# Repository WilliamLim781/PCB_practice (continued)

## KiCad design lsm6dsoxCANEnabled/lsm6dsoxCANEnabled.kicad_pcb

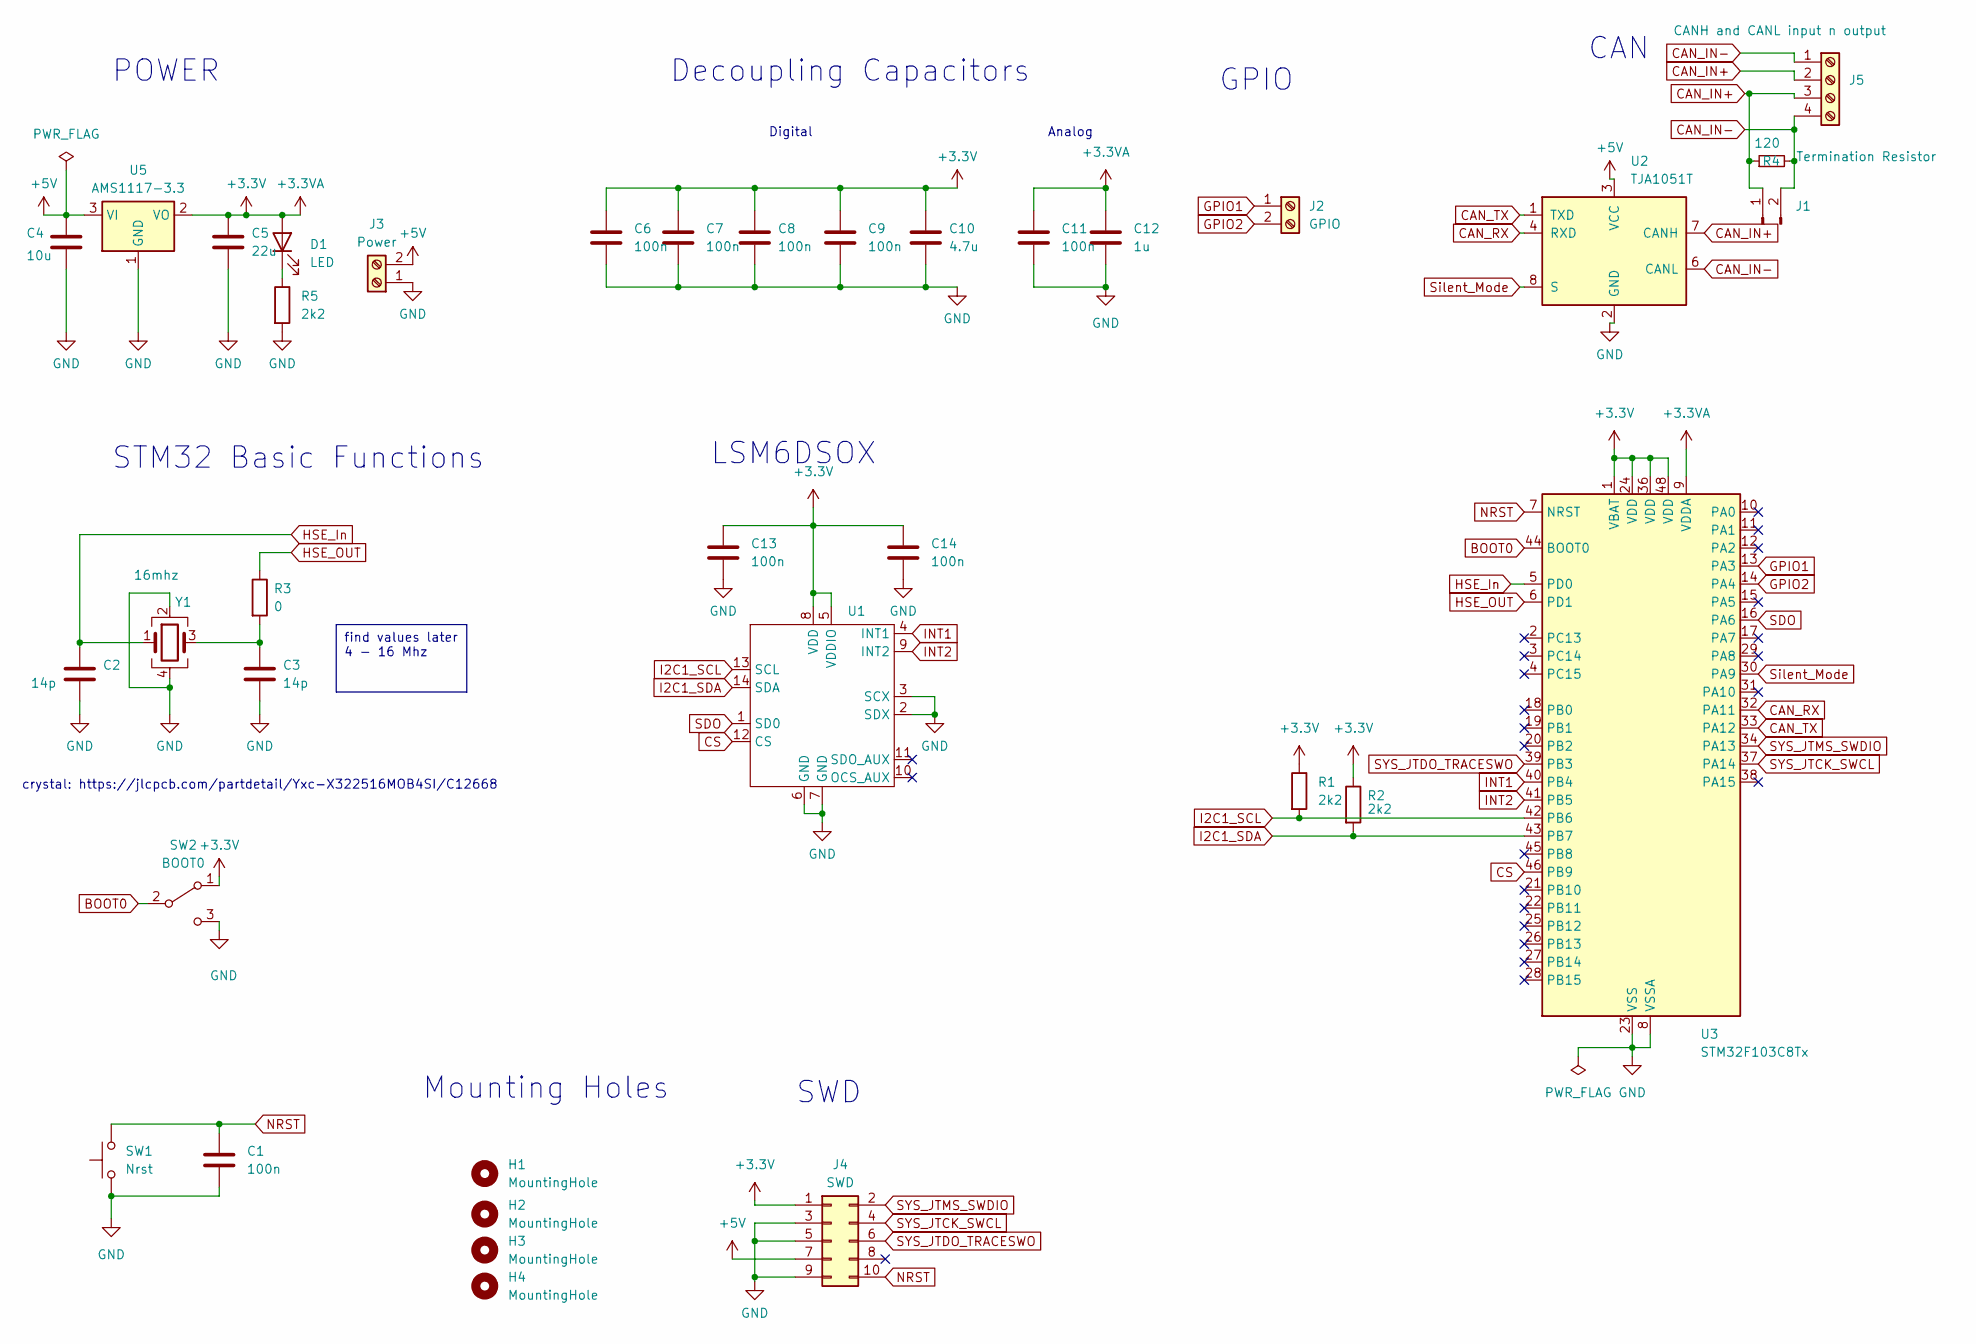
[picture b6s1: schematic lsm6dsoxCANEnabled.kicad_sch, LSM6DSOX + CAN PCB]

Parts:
C1, C6, C7, C8, C9, C11, C13, C14: 100n; C_0603_1608Metric_Pad1.08x0.95mm_HandSolder
C2, C3: 14p; C_0603_1608Metric_Pad1.08x0.95mm_HandSolder
C4: 10u; C_0603_1608Metric_Pad1.08x0.95mm_HandSolder
C5: 22u; C_0805_2012Metric_Pad1.18x1.45mm_HandSolder
C10: 4.7u; C_0603_1608Metric_Pad1.08x0.95mm_HandSolder
C12: 1u; C_0603_1608Metric_Pad1.08x0.95mm_HandSolder
D1: LED; LED_0603_1608Metric_Pad1.05x0.95mm_HandSolder
H1, H2, H3, H4: MountingHole; MountingHole_4mm_Pad_Via
J1: Termination Resistor; PinHeader_1x02_P2.54mm_Vertical
J2: GPIO; TerminalBlock_Phoenix_MKDS-1,5-2_1x02_P5.00mm_Horizontal
J3: Power; TerminalBlock_Phoenix_MKDS-1,5-2_1x02_P5.00mm_Horizontal
J4: SWD; PinHeader_2x05_P2.54mm_Vertical
J5: CANH and CANL input n output; TerminalBlock_Phoenix_MKDS-1,5-4_1x04_P5.00mm_Horizontal
R1, R2, R5: 2k2; R_0603_1608Metric_Pad0.98x0.95mm_HandSolder
R3: 0; R_0603_1608Metric_Pad0.98x0.95mm_HandSolder
R4: 120; R_0603_1608Metric_Pad0.98x0.95mm_HandSolder
SW1: Nrst; SW_SPST_PTS645
SW2: BOOT0; SW_SPDT_CK-JS102011SAQN
U1: LGA-14_3x2.5mm_P0.5mm_LayoutBorder3x4y
U2: TJA1051T; SOIC-8_3.9x4.9mm_P1.27mm
U3: STM32F103C8Tx; LQFP-48_7x7mm_P0.5mm
U5: AMS1117-3.3; SOT-223-3_TabPin2
Y1: 16mhz; Crystal_SMD_3225-4Pin_3.2x2.5mm_HandSoldering

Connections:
+3.3V: C5.1, C6.1, C7.1, C8.1, C9.1, C10.1, C11.1, C12.1, C13.1, C14.1, D1.2 (A), J4.1, R1.1, R2.1, SW2.1 (A), U1.5 (VDDIO), U1.8 (VDD), U3.1 (VBAT), U3.9 (VDDA), U3.24 (VDD), U3.36 (VDD), U3.48 (VDD), U5.2 (VO)
+5V: C4.1, J3.2, J4.7, U2.3 (VCC), U5.3 (VI)
BOOT0: SW2.2 (B), U3.44 (BOOT0)
CAN_IN+: J1.1, J5.2, J5.3, R4.1, U2.7 (CANH)
CAN_IN-: J1.2, J5.1, J5.4, R4.2, U2.6 (CANL)
CAN_RX: U2.4 (RXD), U3.32 (PA11)
CAN_TX: U2.1 (TXD), U3.33 (PA12)
CS: U1.12 (CS), U3.46 (PB9)
GND: C1.2, C2.2, C3.2, C4.2, C5.2, C6.2, C7.2, C8.2, C9.2, C10.2, C11.2, C12.2, C13.2, C14.2, J3.1, J4.3, J4.5, J4.9, R5.2, SW1.1, SW2.3 (C), U1.2 (SDX), U1.3 (SCX), U1.6 (GND), U1.7 (GND), U2.2 (GND), U3.8 (VSSA), U3.23 (VSS), U3.35 (VSS), U3.47 (VSS), U5.1 (GND), Y1.2, Y1.4
GPIO1: J2.1, U3.13 (PA3)
GPIO2: J2.2, U3.14 (PA4)
HSE_In: C2.1, U3.5 (PD0), Y1.1
HSE_OUT: R3.1, U3.6 (PD1)
I2C1_SCL: R1.2, U1.13 (SCL), U3.42 (PB6)
I2C1_SDA: R2.2, U1.14 (SDA), U3.43 (PB7)
INT1: U1.4 (INT1), U3.40 (PB4)
INT2: U1.9 (INT2), U3.41 (PB5)
NRST: C1.1, J4.10, SW1.2, U3.7 (NRST)
unnamed: C3.1, R3.2, Y1.3
unnamed: D1.1 (K), R5.1
SDO: U1.1 (SD0), U3.16 (PA6)
SYS_JTCK_SWCL: J4.4, U3.37 (PA14)
SYS_JTDO_TRACESWO: J4.6, U3.39 (PB3)
SYS_JTMS_SWDIO: J4.2, U3.34 (PA13)
Silent_Mode: U2.8 (S), U3.30 (PA9)

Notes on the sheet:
find values later 4 - 16 Mhz
GPIO
Decoupling Capacitors
crystal: https://jlcpcb.com/partdetail/Yxc-X322516MOB4SI/C12668
SWD
Analog
LSM6DSOX
Mounting Holes
Digital
POWER
STM32 Basic Functions
CAN

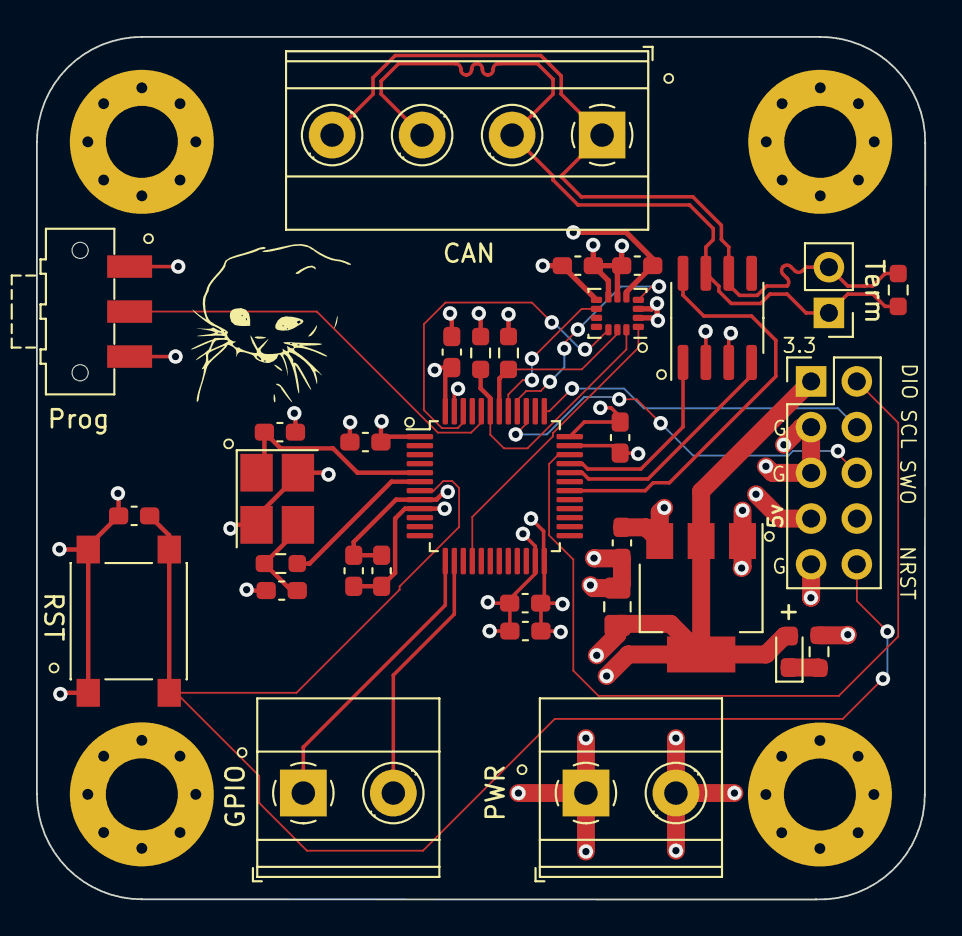
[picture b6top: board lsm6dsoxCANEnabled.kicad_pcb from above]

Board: 4 copper layers, 49.4 x 47.9 mm, 36 parts (0 on the bottom side), 25 nets.

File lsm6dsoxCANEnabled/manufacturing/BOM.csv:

Comment,Designator,FootPrint,JLCPCB PART#
100n,"C1, C6,C7,C8,C9, C11, C13, C14",Capacitor_SMD:C_0603_1608Metric_Pad1.08x0.95mm_HandSolder,C14663
14p,"C2, C3",Capacitor_SMD:C_0603_1608Metric_Pad1.08x0.95mm_HandSolder,C126546
10u,C4,Capacitor_SMD:C_0603_1608Metric_Pad1.08x0.95mm_HandSolder,C386081
22u,C5,Capacitor_SMD:C_0805_2012Metric_Pad1.18x1.45mm_HandSolder,C318688
4.7u,C10,Capacitor_SMD:C_0603_1608Metric_Pad1.08x0.95mm_HandSolder,C711094
1u,C12,Capacitor_SMD:C_0603_1608Metric_Pad1.08x0.95mm_HandSolder,C106858
LED,D1,LED_SMD:LED_0603_1608Metric_Pad1.05x0.95mm_HandSolder,C2290
MountingHole,H1-H4,MountingHole:MountingHole_4mm_Pad_Via,
Termination Resistor ,J1,Connector_PinHeader_2.54mm:PinHeader_1x02_P2.54mm_Vertical,
GPIO,J2,"TerminalBlock_Phoenix:TerminalBlock_Phoenix_MKDS-1,5-2_1x02_P5.00mm_Horizontal",
Power,J3,"TerminalBlock_Phoenix:TerminalBlock_Phoenix_MKDS-1,5-2_1x02_P5.00mm_Horizontal",
SWD,J4,Connector_PinHeader_2.54mm:PinHeader_2x05_P2.54mm_Vertical,
CANH and CANL input n output,J5,"TerminalBlock_Phoenix:TerminalBlock_Phoenix_MKDS-1,5-4_1x04_P5.00mm_Horizontal",
2k2,"R1, R2, R5",Resistor_SMD:R_0603_1608Metric_Pad0.98x0.95mm_HandSolder,C4190
0,R3,Resistor_SMD:R_0603_1608Metric_Pad0.98x0.95mm_HandSolder,C21189
120,R4,Resistor_SMD:R_0603_1608Metric_Pad0.98x0.95mm_HandSolder,C22787
Nrst,SW1,Button_Switch_SMD:SW_SPST_PTS645,C2801823
BOOT0 ,SW2,Button_Switch_SMD:SW_SPDT_CK-JS102011SAQN,C221660
LSM6DSOX,U1,Package_LGA:LGA-14_3x2.5mm_P0.5mm_LayoutBorder3x4y,C481766
TJA1051T,U2,Package_SO:SOIC-8_3.9x4.9mm_P1.27mm,"
C7432801"
STM32F103C8Tx,U3,Package_QFP:LQFP-48_7x7mm_P0.5mm,C8734
AMS1117CD-3.3,    U5,Package_TO_SOT_SMD:SOT-223-3_TabPin2,C6186
16mhz,Y1,Crystal:Crystal_SMD_3225-4Pin_3.2x2.5mm_HandSoldering,C12668

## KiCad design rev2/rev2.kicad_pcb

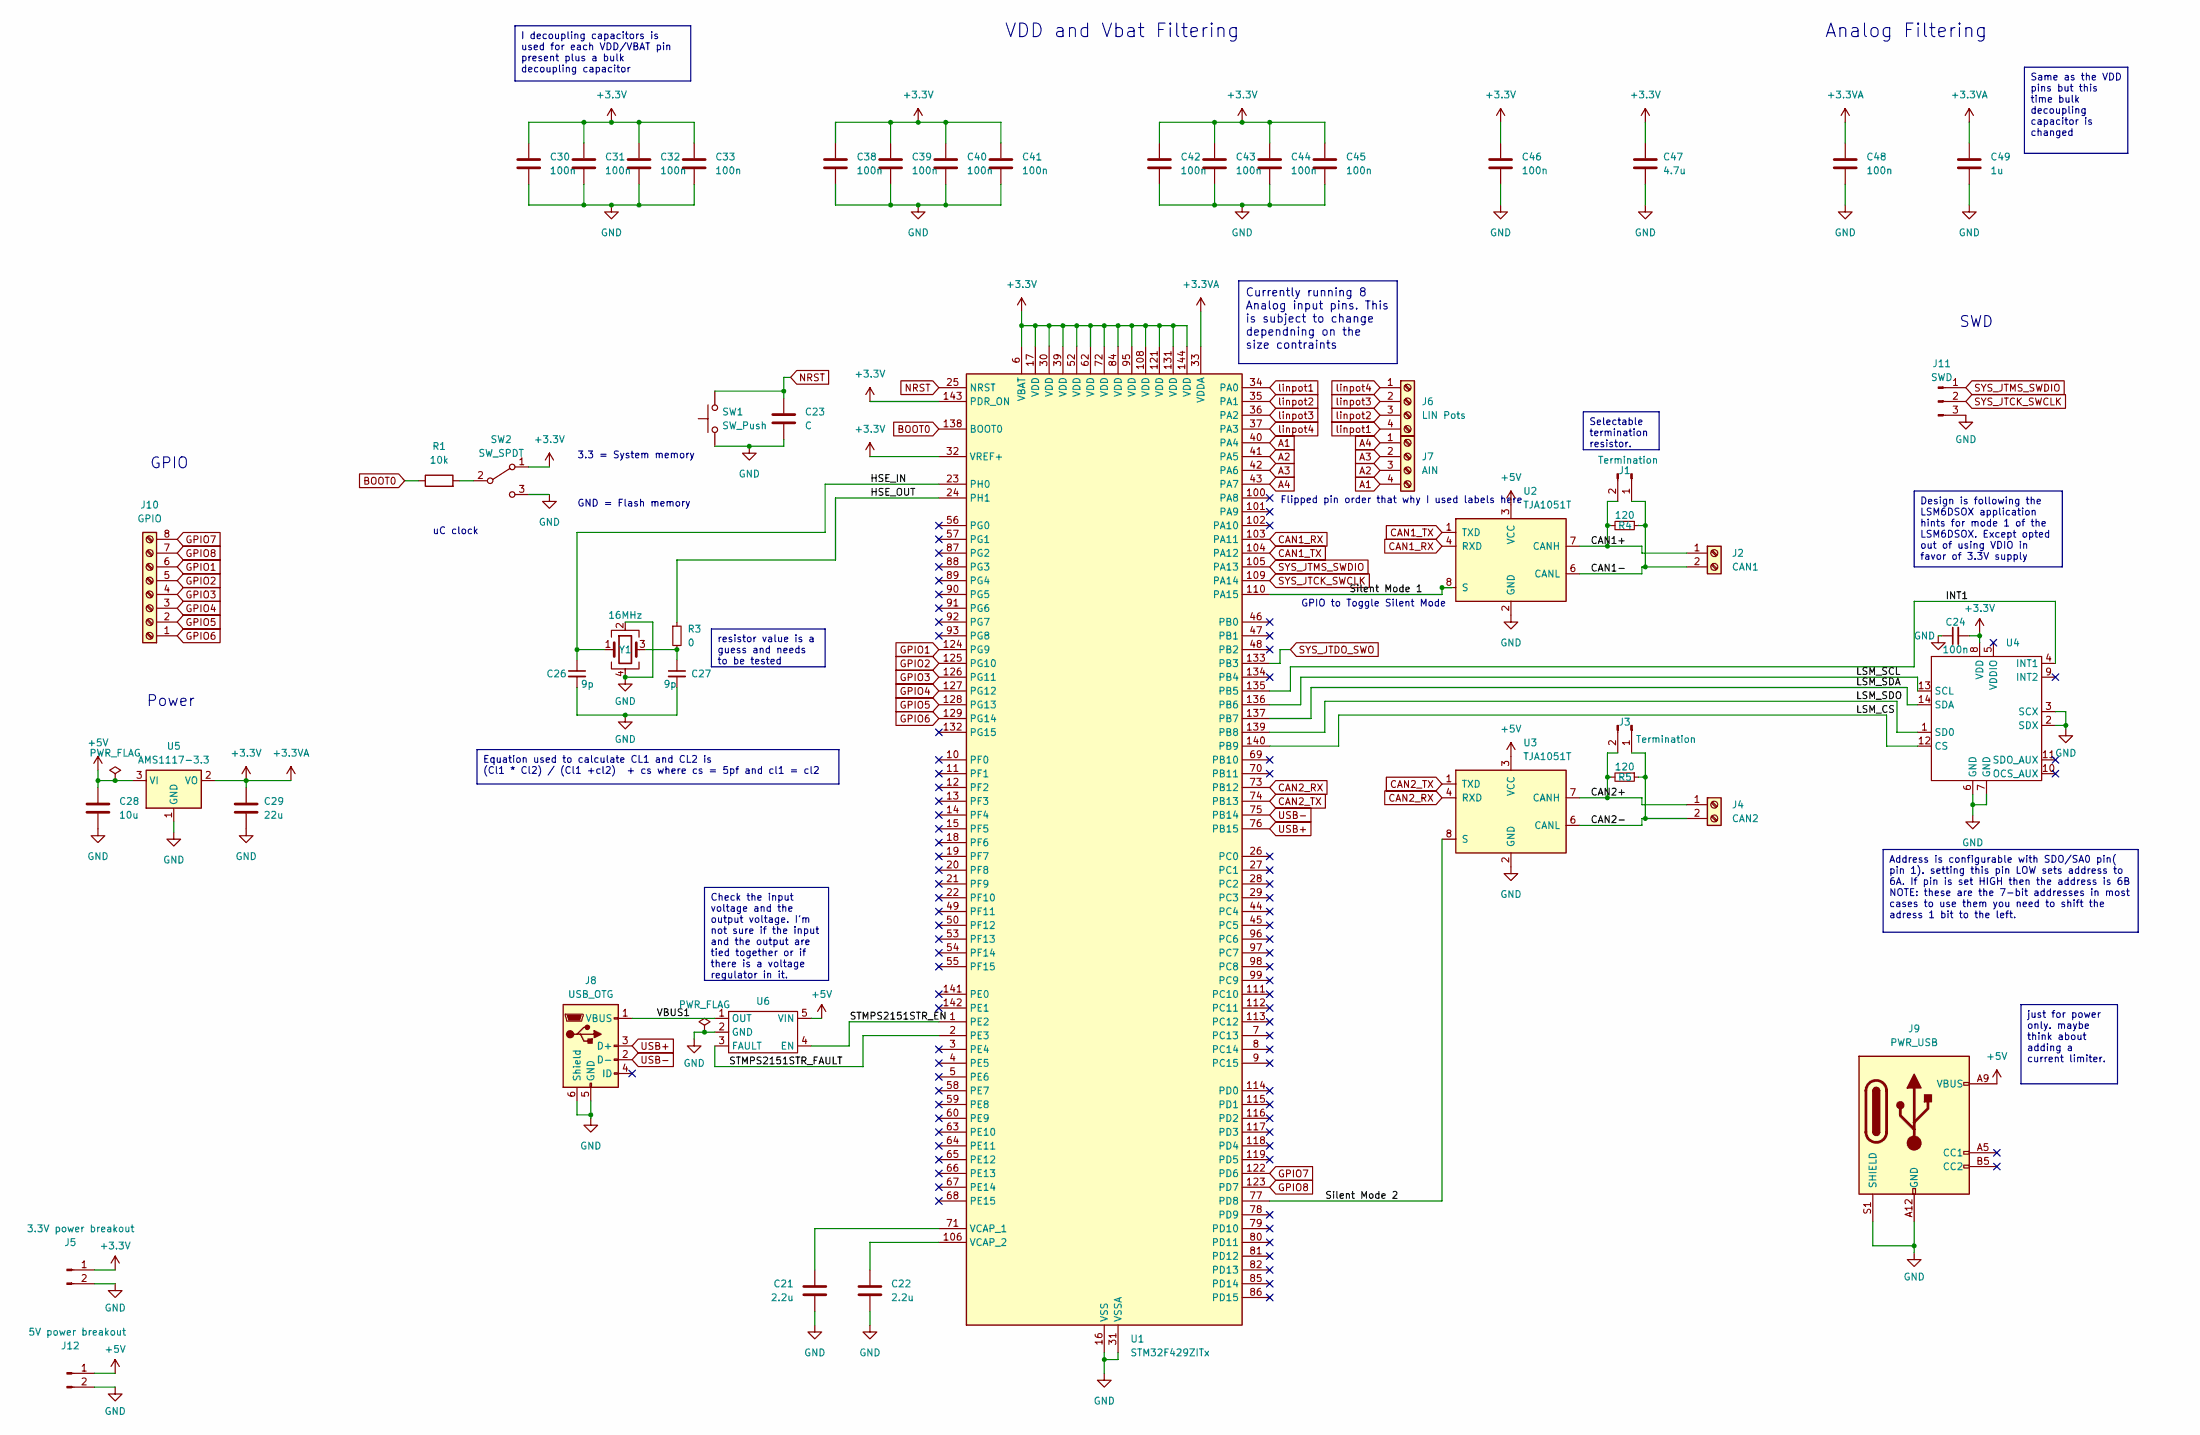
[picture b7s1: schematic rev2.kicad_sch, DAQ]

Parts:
C21, C22: 2.2u; C_0603_1608Metric_Pad1.08x0.95mm_HandSolder
C23: C; C_0603_1608Metric_Pad1.08x0.95mm_HandSolder
C24, C30, C31, C32, C33, C38, C39, C40, C41, C42, C43, C44, C45, C46, C48: 100n; C_0603_1608Metric_Pad1.08x0.95mm_HandSolder
C26, C27: 9p; C_0603_1608Metric_Pad1.08x0.95mm_HandSolder
C28: 10u; C_0603_1608Metric_Pad1.08x0.95mm_HandSolder
C29: 22u; C_0603_1608Metric_Pad1.08x0.95mm_HandSolder
C47: 4.7u; C_0603_1608Metric_Pad1.08x0.95mm_HandSolder
C49: 1u; C_0603_1608Metric_Pad1.08x0.95mm_HandSolder
J1, J3: Termination; PinHeader_1x02_P2.54mm_Vertical
J2: CAN1; TerminalBlock_Phoenix_MPT-0,5-2-2.54_1x02_P2.54mm_Horizontal
J4: CAN2; TerminalBlock_Phoenix_MPT-0,5-2-2.54_1x02_P2.54mm_Horizontal
J5: 3.3V power breakout; PinHeader_1x02_P2.54mm_Vertical
J6: LIN Pots; TerminalBlock_Phoenix_MPT-0,5-4-2.54_1x04_P2.54mm_Horizontal
J7: AIN; TerminalBlock_Phoenix_MPT-0,5-4-2.54_1x04_P2.54mm_Horizontal
J8: USB_OTG; USB_Mini-B_Wuerth_65100516121_Horizontal
J9: PWR_USB; USB_C_Receptacle_GCT_USB4105-xx-A_16P_TopMnt_Horizontal
J10: GPIO; TerminalBlock_Phoenix_MPT-0,5-8-2.54_1x08_P2.54mm_Horizontal
J11: SWD; PinHeader_1x03_P2.54mm_Vertical
J12: 5V power breakout; PinHeader_1x02_P2.54mm_Vertical
R1: 10k; R_0603_1608Metric_Pad0.98x0.95mm_HandSolder
R3: 0; R_0603_1608Metric_Pad0.98x0.95mm_HandSolder
R4, R5: 120; R_0603_1608Metric_Pad0.98x0.95mm_HandSolder
SW1: SW_Push; SW_SPST_PTS645
SW2: SW_SPDT; SW_SPDT_PCM12
U1: STM32F429ZITx; LQFP-144_20x20mm_P0.5mm
U2, U3: TJA1051T; SOIC-8_3.9x4.9mm_P1.27mm
U4: Bosch_LGA-14_3x2.5mm_P0.5mm
U5: AMS1117-3.3; SOT-223-3_TabPin2
U6: SOT-23-5_HandSoldering
Y1: 16MHz; Crystal_SMD_3225-4Pin_3.2x2.5mm

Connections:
+3.3V: C24.2, C29.1, C30.1, C31.1, C32.1, C33.1, C38.1, C39.1, C40.1, C41.1, C42.1, C43.1, C44.1, C45.1, C46.1, C47.1, C48.1, C49.1, J5.1, SW2.1 (A), U1.6 (VBAT), U1.17 (VDD), U1.30 (VDD), U1.32 (VREF+), U1.33 (VDDA), U1.39 (VDD), U1.52 (VDD), U1.62 (VDD), U1.72 (VDD), U1.84 (VDD), U1.95 (VDD), U1.108 (VDD), U1.121 (VDD), U1.131 (VDD), U1.143 (PDR_ON), U1.144 (VDD), U4.8 (VDD), U5.2 (VO)
+5V: C28.1, J9.A9 (VBUS), J9.B9 (VBUS), J12.1, U2.3 (VCC), U3.3 (VCC), U5.3 (VI), U6.5 (VIN)
/CAN1+: J1.2, J2.1, R4.2, U2.7 (CANH)
/CAN1-: J1.1, J2.2, R4.1, U2.6 (CANL)
/CAN2+: J3.2, J4.1, R5.2, U3.7 (CANH)
/CAN2-: J3.1, J4.2, R5.1, U3.6 (CANL)
/HSE_IN: C26.1, U1.23 (PH0), Y1.1
/HSE_OUT: R3.1, U1.24 (PH1)
/INT1: U1.135 (PB5), U4.4 (INT1)
/LSM_CS: U1.140 (PB9), U4.12 (CS)
/LSM_SCL: U1.136 (PB6), U4.13 (SCL)
/LSM_SDA: U1.137 (PB7), U4.14 (SDA)
/LSM_SDO: U1.139 (PB8), U4.1 (SD0)
/STMPS2151STR_EN: U1.1 (PE2), U6.4 (EN)
/STMPS2151STR_FAULT: U1.2 (PE3), U6.3 (FAULT)
/Silent Mode 1: U1.110 (PA15), U2.8 (S)
/Silent Mode 2: U1.77 (PD8), U3.8 (S)
/VBUS1: J8.1 (VBUS), U6.1 (OUT)
A1: J7.4, U1.40 (PA4)
A2: J7.3, U1.41 (PA5)
A3: J7.2, U1.42 (PA6)
A4: J7.1, U1.43 (PA7)
BOOT0: R1.1, U1.138 (BOOT0)
CAN1_RX: U1.103 (PA11), U2.4 (RXD)
CAN1_TX: U1.104 (PA12), U2.1 (TXD)
CAN2_RX: U1.73 (PB12), U3.4 (RXD)
CAN2_TX: U1.74 (PB13), U3.1 (TXD)
GND: C21.2, C22.2, C23.2, C24.1, C26.2, C27.2, C28.2, C29.2, C30.2, C31.2, C32.2, C33.2, C38.2, C39.2, C40.2, C41.2, C42.2, C43.2, C44.2, C45.2, C46.2, C47.2, C48.2, C49.2, J5.2, J8.5 (GND), J8.6 (Shield), J9.A12 (GND), J9.B12 (GND), J9.S1 (SHIELD), J11.3, J12.2, SW1.1, SW2.3 (C), U1.16 (VSS), U1.31 (VSSA), U1.38 (VSS), U1.51 (VSS), U1.61 (VSS), U1.83 (VSS), U1.94 (VSS), U1.107 (VSS), U1.120 (VSS), U1.130 (VSS), U2.2 (GND), U3.2 (GND), U4.2 (SDX), U4.3 (SCX), U4.6 (GND), U4.7 (GND), U5.1 (GND), U6.2 (GND), Y1.2, Y1.4
GPIO1: J10.6, U1.124 (PG9)
GPIO2: J10.5, U1.125 (PG10)
GPIO3: J10.4, U1.126 (PG11)
GPIO4: J10.3, U1.127 (PG12)
GPIO5: J10.2, U1.128 (PG13)
GPIO6: J10.1, U1.129 (PG14)
GPIO7: J10.8, U1.122 (PD6)
GPIO8: J10.7, U1.123 (PD7)
NRST: C23.1, SW1.2, U1.25 (NRST)
unnamed: C27.1, R3.2, Y1.3
unnamed: R1.2, SW2.2 (B)
unnamed: C21.1, U1.71 (VCAP_1)
unnamed: C22.1, U1.106 (VCAP_2)
SYS_JTCK_SWCLK: J11.2, U1.109 (PA14)
SYS_JTDO_SWO: U1.133 (PB3)
SYS_JTMS_SWDIO: J11.1, U1.105 (PA13)
USB+: J8.3 (D+), U1.76 (PB15)
USB-: J8.2 (D-), U1.75 (PB14)
linpot1: J6.4, U1.34 (PA0)
linpot2: J6.3, U1.35 (PA1)
linpot3: J6.2, U1.36 (PA2)
linpot4: J6.1, U1.37 (PA3)

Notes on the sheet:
Design is following the LSM6DSOX application hints for mode 1 of the LSM6DSOX. Except opted out of using VDIO in favor of 3.3V supply
resistor value is a guess and needs to be tested
just for power only. maybe think about adding a current limiter.
Check the input voltage and the output voltage. I'm not sure if the input and the output are tied together or if there is a voltage regulator in it.
Equation used to calculate CL1 and CL2 is (Cl1 * Cl2) / (Cl1 +cl2) + cs where cs = 5pf and cl1 = cl2
Currently running 8 Analog input pins. This is subject to change dependning on the size contraints
Selectable termination resistor.
Address is configurable with SDO/SA0 pin( pin 1). setting this pin LOW sets address to 6A. If pin is set HIGH then the address is 6B NOTE: these are the 7-bit addresses in most cases to use them you need to shift the adress 1 bit to the left.
I decoupling capacitors is used for each VDD/VBAT pin present plus a bulk decoupling capacitor
Same as the VDD pins but this time bulk decoupling capacitor is changed
GPIO
3.3 = System memory
Flipped pin order that why I used labels here
SWD
GPIO to Toggle Silent Mode
uC clock
VDD and Vbat Filtering
Analog Filtering
Power
GND = Flash memory

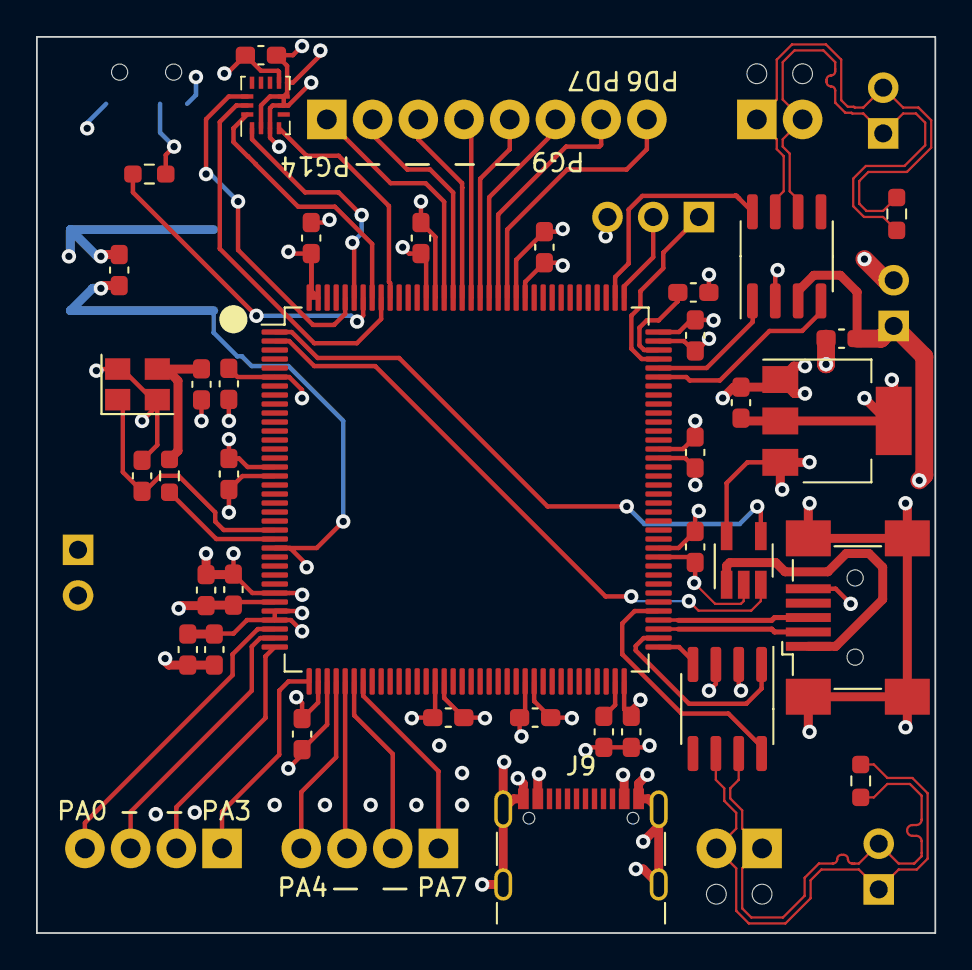
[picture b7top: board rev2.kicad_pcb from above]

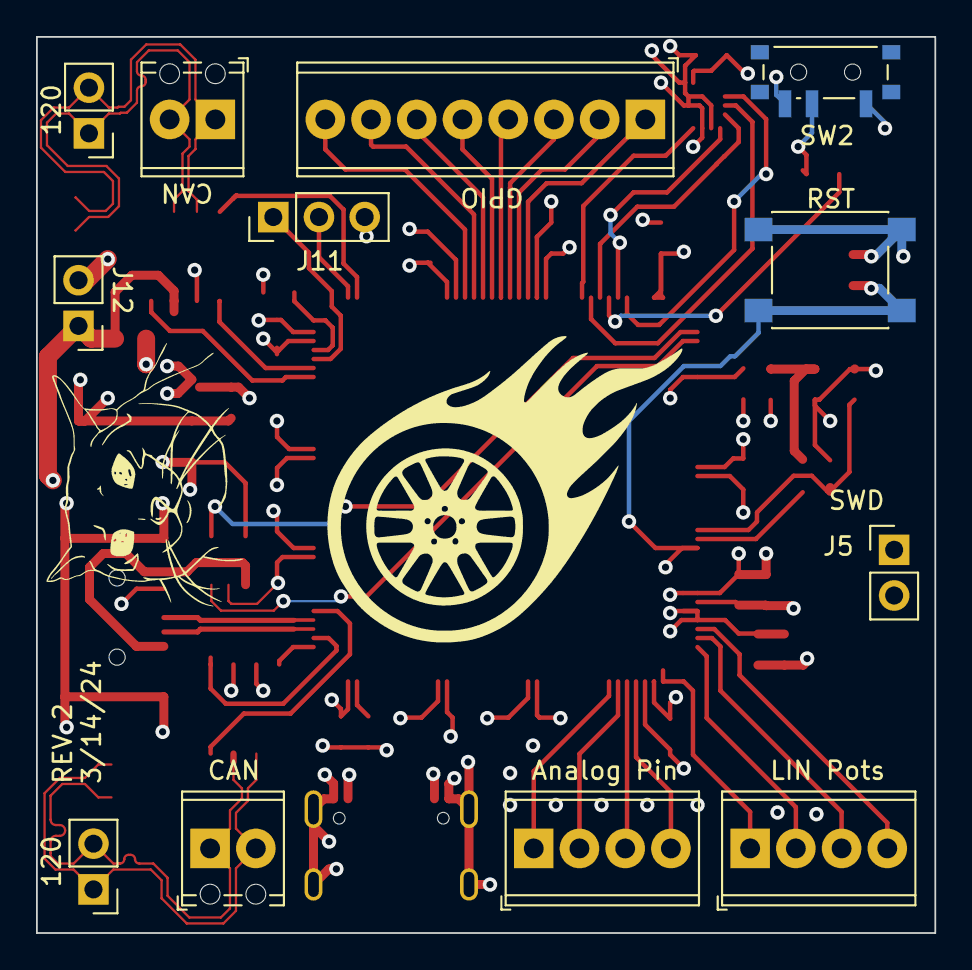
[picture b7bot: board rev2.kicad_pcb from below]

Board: 4 copper layers, 49.9 x 49.8 mm, 49 parts (12 on the bottom side), 49 nets.

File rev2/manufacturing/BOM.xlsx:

Comment | Designator | FootPrint | JLCPCB PART#
2.2u | C21,C22,C23 | 603 | C76612
100n | C24, C30-33, C38-46, C48 | 603 | C88219
9p | C26,C27 | 603 | C282512
10u | C28 | 603 | C91150
22u | C29 | 603 | C84419
4.7u | C47 | 603 | C86016
1u | C49 | 603 | C76617
STM32F429ZITx | U1 | LQFP144 | C84808
USB_OTG | J8
PWR_USB | J9
10k | R1 | 603 | C191124
120 | R4, R5 | 603 | C177673
0 | R3 | 603
SW_Push | SW1 | SPST_PTS645
SW2 | SW_SPDT | PCM12
TJA1051T | U2, U3 | SOIC-8 | C5342108
LSM6DSOX | U4 | LGA-14 | C481766
AMS1117-3.3 | U5 | SOT-223-3 | C6186
 | U6 | SOT-23 | C135998
16MHz | Y1 | SMD_3225

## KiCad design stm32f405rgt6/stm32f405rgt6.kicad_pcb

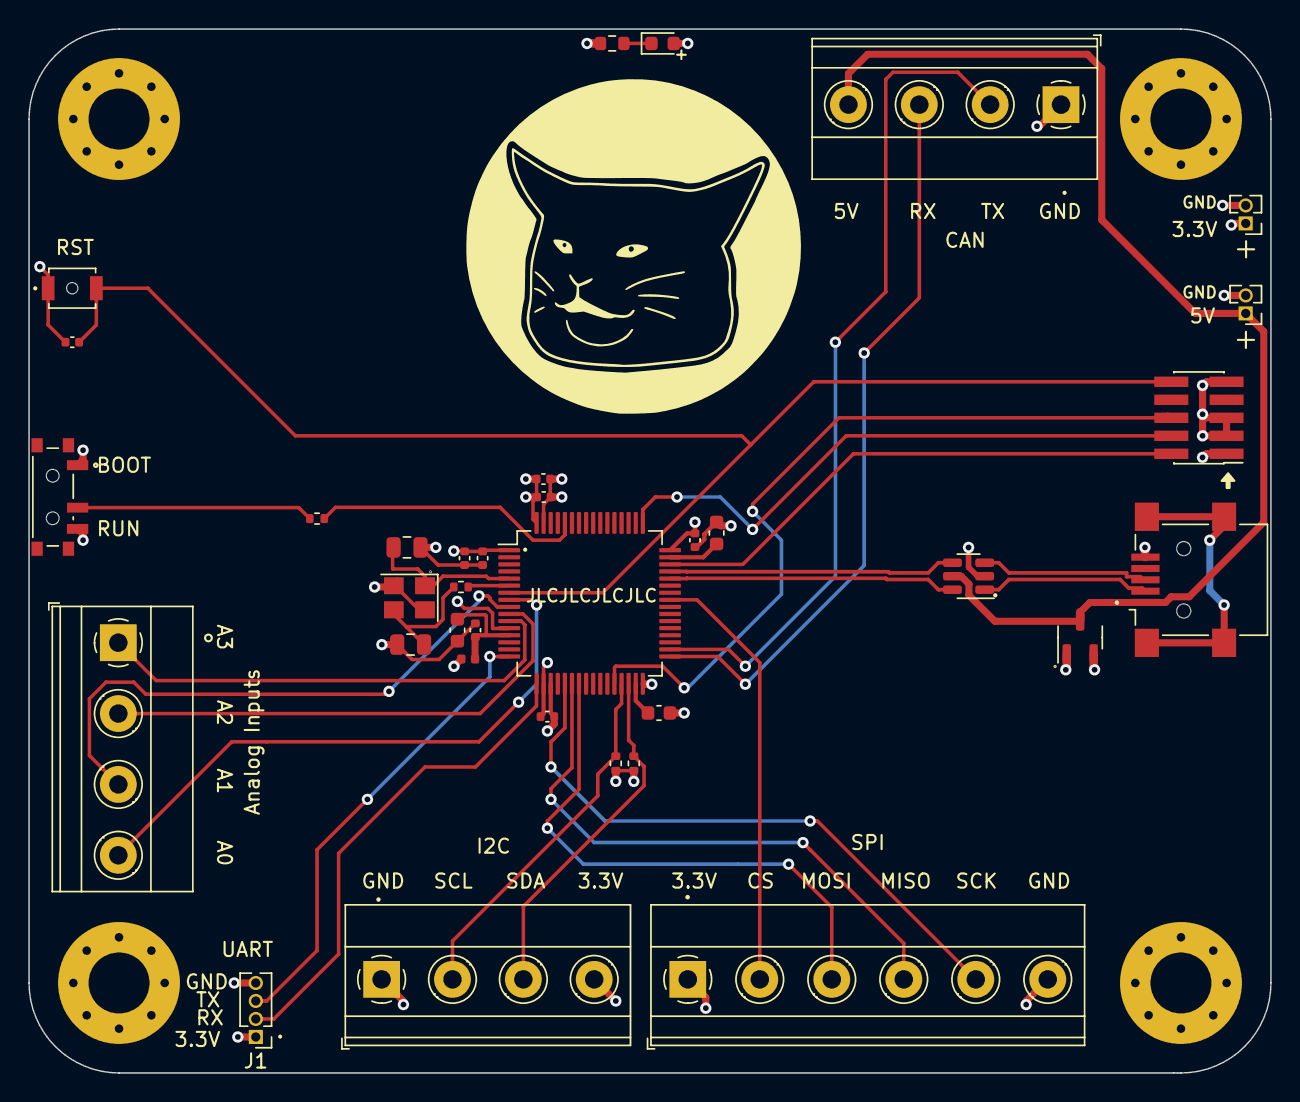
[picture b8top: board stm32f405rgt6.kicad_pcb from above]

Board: 4 copper layers, 87.6 x 73.7 mm, 39 parts (0 on the bottom side), 34 nets.

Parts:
Analog Inputs: AnalogInptus; TerminalBlock_Phoenix_MKDS-1,5-4_1x04_P5.00mm_Horizontal
C1: 1u; C_0402_1005Metric
C2, C3, C4, C5, C6: 100n; C_0402_1005Metric
C7: 4u7; C_0603_1608Metric
C8: 10n; C_0402_1005Metric
C9: .1u; C_0402_1005Metric
C10, C11: 14pf; C_0805_2012Metric
C12, C13: 2u2; C_0603_1608Metric
D1: LED; LED_0603_1608Metric
H1, H2, H3, H4: MountingHole_Pad; MountingHole_4.3mm_M4_Pad_Via
I2C: I2C; TerminalBlock_Phoenix_MKDS-1,5-4_1x04_P5.00mm_Horizontal
J1: USART; PinHeader_1x04_P1.27mm_Vertical
J2: SWD; PinHeader_2x05_P1.27mm_Vertical_SMD
J4: USB_OTG; USB_Mini-B_Lumberg_2486_01_Horizontal
J7: 5V; PinHeader_1x02_P1.27mm_Vertical
J8: CAN; TerminalBlock_Phoenix_MKDS-1,5-4_1x04_P5.00mm_Horizontal
J9: 3.3V; PinHeader_1x02_P1.27mm_Vertical
L1: 39n; L_0402_1005Metric
R1, R2: 2k2; R_0402_1005Metric
R3: 10k; R_0402_1005Metric
R4: 47; R_0402_1005Metric
R5: 1k5; R_0603_1608Metric
SPI: SPI; TerminalBlock_Phoenix_MKDS-1,5-6-5.08_1x06_P5.08mm_Horizont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
SW1: SW_Push; SW_SPST_B3U-1000P-B
SW2: Boot0 selector; SW_SPDT_PCM12
U1: USBLC6-2SC6; SOT-23-6
U2: STM32F405RGT6; LQFP-64_10x10mm_P0.5mm
XC6206P332MR1: SOT-23-3
Y1: 25Mhz; Crystal_SMD_3225-4Pin_3.2x2.5mm

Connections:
+3.3V: C1.1, C2.1, C3.1, C4.1, C5.1, C6.1, D1.2 (A), I2C.4, J1.1, J2.1, J9.1, L1.1, R1.2, R2.1, SPI.1, SW2.1 (A), U2.1 (VBAT), U2.19 (VDD), U2.32 (VDD), U2.48 (VDD), U2.64 (VDD), XC6206P332MR1.2 (Vout)
+3.3VA: C7.1, C8.1, L1.2, U2.13 (VDDA)
+5V: J4.1 (VBUS), J7.1, J8.4, U1.5 (VBUS), XC6206P332MR1.3 (Vin)
/R_ext: C11.2, R4.2, Y1.3
BOOT0: R3.1, U2.60 (BOOT0)
CAN_RX: J8.3, U2.33 (PB12)
CAN_TX: J8.2, U2.34 (PB13)
GND: C1.2, C2.2, C3.2, C4.2, C5.2, C6.2, C7.2, C8.2, C9.2, C10.1, C11.1, C12.2, C13.2, H1.1, H2.1, H3.1, H4.1, I2C.1, J1.4, J2.3, J2.5, J2.9, J4.5 (GND), J7.2, J8.1, J9.2, R5.2, SPI.6, SW1.1, SW2.3 (C), U1.2 (GND), U2.12 (VSSA), U2.18 (VSS), U2.63 (VSS), XC6206P332MR1.1 (GND), Y1.2, Y1.4
HSE_IN: C10.2, U2.5 (PH0), Y1.1
HSE_OUT: R4.1, U2.6 (PH1)
I2C2_SCL: I2C.2, R2.2, U2.29 (PB10)
I2C2_SDA: I2C.3, R1.1, U2.30 (PB11)
LinPot1: Analog Inputs.4, U2.8 (PC0)
LinPot2: Analog Inputs.3, U2.9 (PC1)
LinPot3: Analog Inputs.2, U2.10 (PC2)
LinPot4: Analog Inputs.1, U2.11 (PC3)
NRST: C9.1, J2.10, SW1.2, U2.7 (NRST)
unnamed: D1.1 (K), R5.1
unnamed: R3.2, SW2.2 (B)
unnamed: C12.1, U2.31 (VCAP_1)
unnamed: C13.1, U2.47 (VCAP_2)
SPI1_CS: SPI.2, U2.41 (PA8)
SPI1_MISO: SPI.4, U2.22 (PA6)
SPI1_MOSI: SPI.3, U2.23 (PA7)
SPI1_SCK: SPI.5, U2.21 (PA5)
SWCLK: J2.4, U2.49 (PA14)
SWDIO: J2.2, U2.46 (PA13)
SWO: J2.6, U2.28 (PB2)
USART2_RX: J1.2, U2.17 (PA3)
USART2_TX: J1.3, U2.16 (PA2)
USB+: U1.4 (I/O2), U2.45 (PA12)
USB-: U1.6 (I/O1), U2.44 (PA11)
USB_CON+: J4.3 (D+), U1.3 (I/O2)
USB_CON-: J4.2 (D-), U1.1 (I/O1)
